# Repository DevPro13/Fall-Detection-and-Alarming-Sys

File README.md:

# Fall Detection and Alerting System

> "Fall seven times, stand up eight." - Japanese Proverb

While the proverb speaks of resilience, falls can be a critical health concern, especially for the elderly. This project presents a robust fall detection system that combines wearable technology and machine learning to provide timely alerts, mitigating the risks associated with delayed assistance.

This system is built upon the research detailed in the paper [**"Fall Detection System for Elderly People Using LSTM"**](https://www.nepjol.info/index.php/joeis/article/view/93497), [Alternate Link](https://www.researchgate.net/publication/404278061_Fall_Detection_System_for_Elderly_People_Using_LSTM). *(Link to full paper — https://www.nepjol.info/index.php/joeis/article/view/93497 or https://www.researchgate.net/publication/404278061_Fall_Detection_System_for_Elderly_People_Using_LSTM)* It leverages a custom-designed wearable device to monitor user movement and a sophisticated deep learning model to accurately distinguish between normal daily activities and dangerous falls.

The system is architecturally divided into two main sub-systems:
-   **Wearable Detector:** A compact, body-worn device that captures real-time motion data.
-   **System Groundstation:** A stationary unit that receives alerts from the wearable and triggers local alarms.

## System Activity Diagram
The operational flow of the system is as follows:

## Wearable Detector

This is the core data acquisition and processing unit of the system. It is designed to be worn on the user's shoulder—a location chosen to minimize motion impedance and ensure stable, accurate readings. The device continuously captures motion data, processes it with an onboard machine learning model, and transmits an alert if a fall is detected.

**Key Components:**
*   **Microcontroller:** Raspberry Pi Pico (RP2040)
*   **Sensor:** MPU-6050, a 6-axis Inertial Measurement Unit (IMU) that provides accelerometer and gyroscope data.
*   **Wireless Communication:** The hardware is designed with a dedicated slot for an HC-05 Bluetooth module to transmit alerts wirelessly to the groundstation.
*   **Power Supply:** The device can be powered via a DC source (regulated by an LM7805 IC) or a direct USB connection.

### Machine Learning Model

The intelligence of the system lies in its fall detection model. Instead of simple thresholds, this project employs a **Long Short-Term Memory (LSTM)** neural network, a type of recurrent neural network (RNN) ideal for analyzing sequential data like human motion.

*   **Model Architecture:** The final system uses a refined **double-layer LSTM model**. This architecture proved significantly more effective than an initial single-layer model, demonstrating a superior ability to learn the complex temporal patterns that differentiate a fall from other activities.
*   **Data Collection:** The model was trained on a dataset created by capturing sequential motion data from participants mimicking the daily activities of the elderly (walking, sitting, standing) as well as simulated fall events.
*   **Performance:** The double-layer LSTM model achieved an impressive **accuracy of 97.8%**. More critically, it demonstrated high sensitivity in identifying falls, reducing the dangerous instances of false negatives that plagued simpler models.

| Metric | 1-Layer LSTM Model | 2-Layer LSTM Model |
| :--- | :--- | :--- |
| **Accuracy** | 92.19% | **97.8%** |
| **Sensitivity (Recall)** | 38.37% | **91.86%** |
| **Precision** | 75.00% | **87.78%** |
| **F1-Score** | 50.77% | **89.77%** |

The trained model is deployed directly onto the Raspberry Pi Pico, allowing for real-time, on-device inference without reliance on a constant internet connection.

### PCB Design

## System Groundstation

The groundstation acts as the central alerting hub. It remains in a fixed location within the user's home, listening for signals from the wearable device. Upon receiving a fall alert, it triggers both audible and visual alarms to notify nearby caregivers.

**Key Components:**
*   **Microcontroller:** Atmega328p
*   **Wireless Communication:** An RF/Bluetooth receiver to communicate with the wearable device.
*   **Alerting Peripherals:** A loud buzzer and bright LEDs.
*   **Power Supply:** 5V DC power, supplied by the custom rectifier circuit below.

## Power Supply Rectifier

This custom circuit was designed to provide a stable, regulated 5V DC supply for the groundstation from an AC source.

**Components:**
*   Bridge Rectifier (Diodes)
*   LM7805 Voltage Regulator
*   Smoothing Capacitors
*   Resistor

### PCB Design

## Authors

- **Sanim Kumar Khatri** - [GitHub](https://github.com/SanimKumarKhatri)
- **Devraj Parajuli** - [GitHub](https://github.com/DevPro13)
- **Bhupendra Chaulagain**- [Github](https://github.com/BhupendraChaulagain)
- **Prayag Man Mane** - [Github](https://github.com/gityag)
- **Sandesh Thapa** - [Github](https://github.com/sandeshit)\
IOE, Pulchowk Campus

## License

This project is released for academic and research purposes. Hardware designs and firmware are provided as-is.

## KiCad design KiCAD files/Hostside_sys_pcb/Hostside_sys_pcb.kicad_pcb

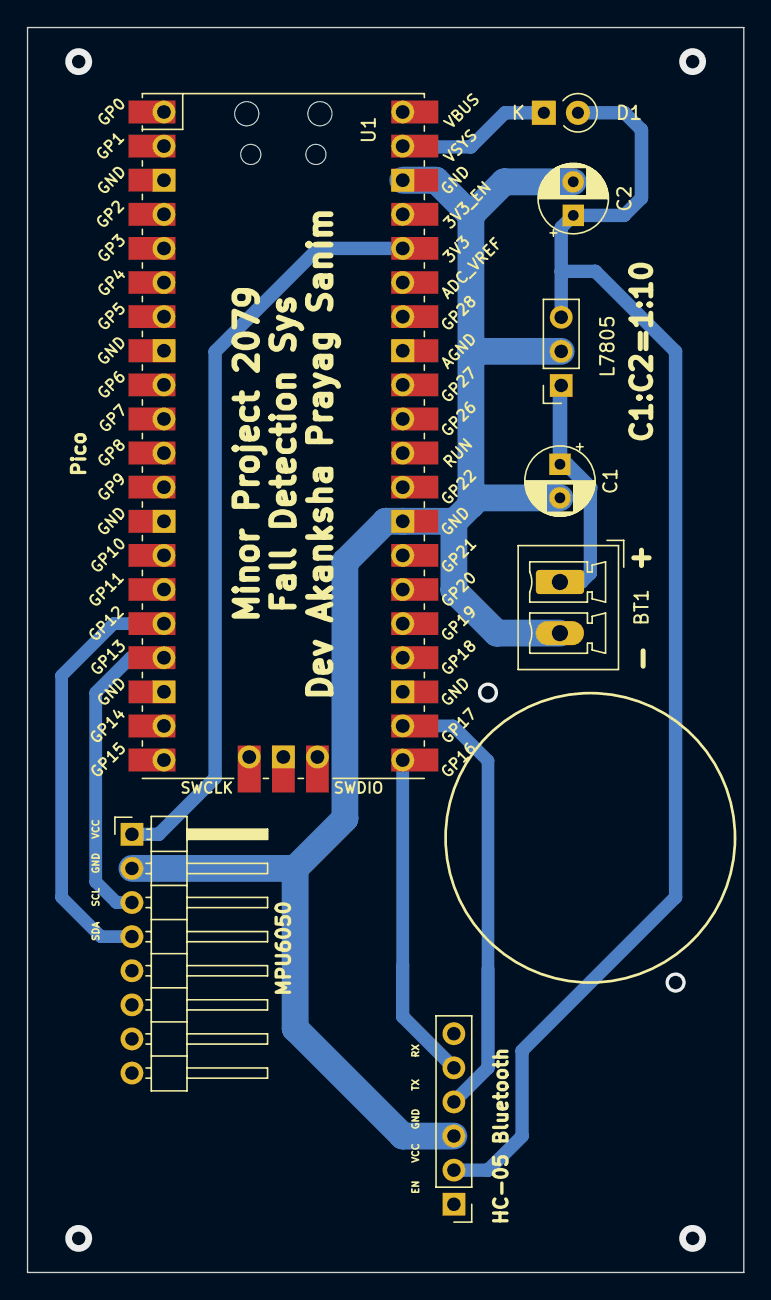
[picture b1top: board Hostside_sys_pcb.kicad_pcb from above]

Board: 2 copper layers, 53.3 x 92.7 mm, 8 parts (0 on the bottom side), 9 nets.

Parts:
BT1: Battery_Cell; PhoenixContact_MCV_1,5_2-G-3.81_1x02_P3.81mm_Vertical
C1, C2: C; CP_Radial_D5.0mm_P2.50mm
D1: MBR1020VL; D_A-405_P2.54mm_Vertical_KathodeUp
HC-05 Bluetooth: Conn_01x06_Female; PinHeader_1x06_P2.54mm_Vertical
MPU6050: Conn_01x08_Female; PinHeader_1x08_P2.54mm_Horizontal
U1: Pico; RPi_Pico_SMD_TH
U2: L7805; PinSocket_1x03_P2.54mm_Vertical

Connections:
/SCL: MPU6050.3, U1.17 (GPIO13)
/SDA: MPU6050.4, U1.16 (GPIO12)
/VCC_3.3: MPU6050.1, U1.36 (3V3)
/Vin_5V: C2.1, D1.2 (A), HC-05 Bluetooth.2, U2.3 (OUT)
/rx: HC-05 Bluetooth.4, U1.22 (GPIO17)
/tx: HC-05 Bluetooth.5, U1.21 (GPIO16)
GND: BT1.2 (-), C1.2, C2.2, HC-05 Bluetooth.3, MPU6050.2, U1.28 (GND), U1.38 (GND), U2.2 (GND)
unnamed: BT1.1 (+), C1.1, U2.1 (IN)
unnamed: D1.1 (K), U1.39 (VSYS)

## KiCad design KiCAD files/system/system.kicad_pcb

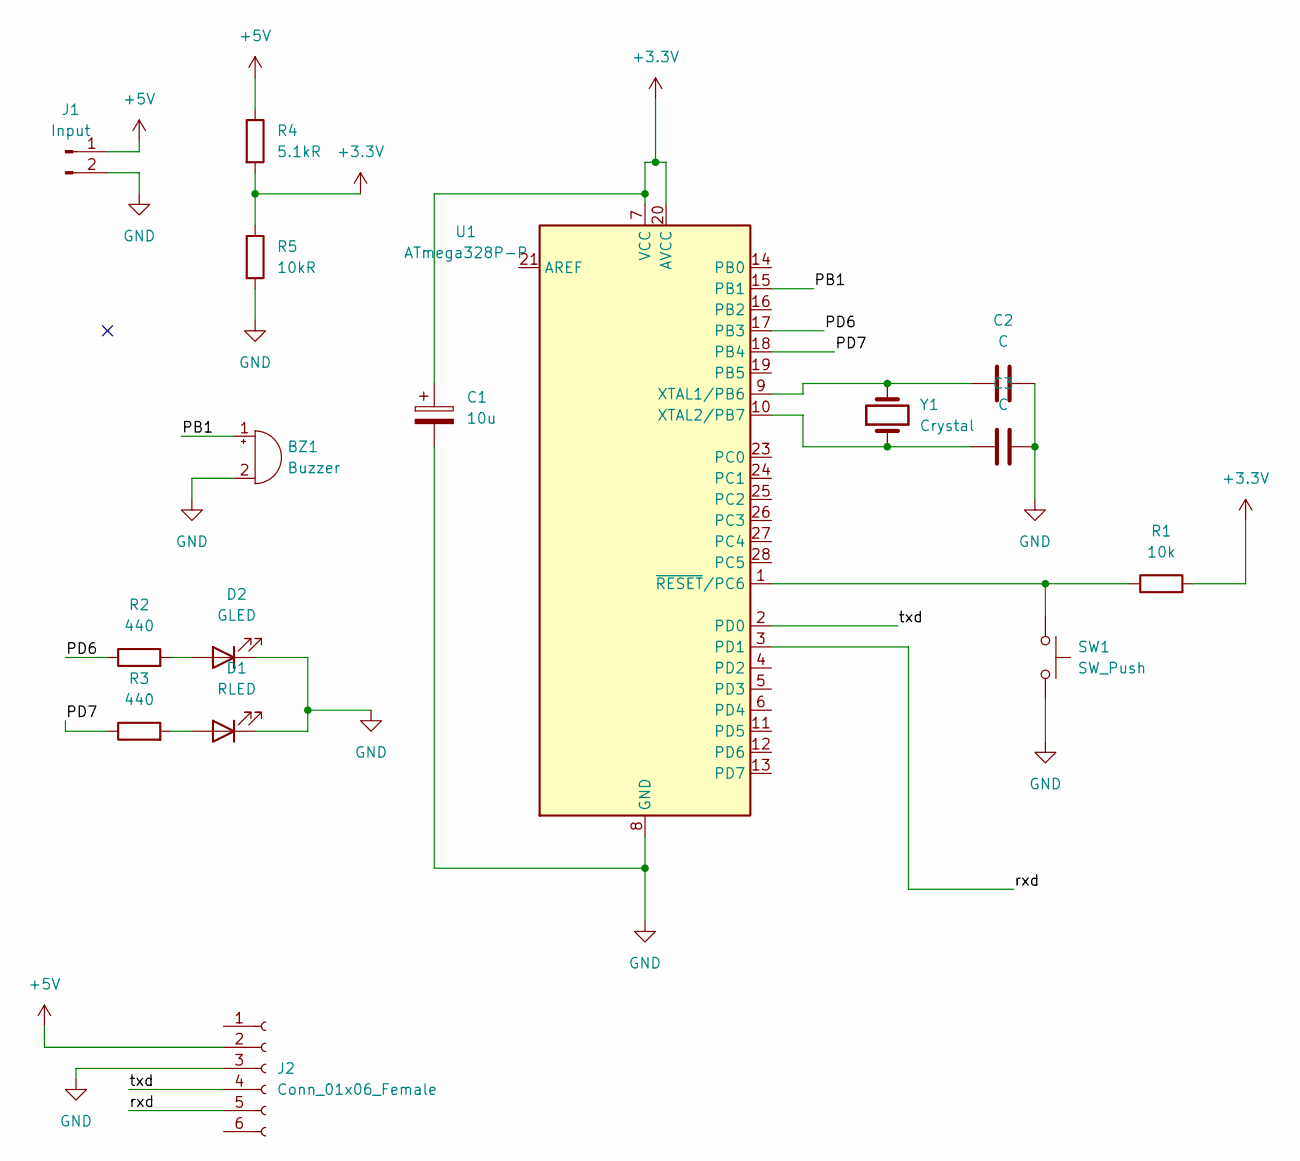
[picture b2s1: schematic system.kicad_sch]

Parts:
BZ1: Buzzer; MagneticBuzzer_ProSignal_ABT-410-RC
C1: 10u; CP_Radial_D5.0mm_P2.00mm
C2, C3: C; C_Disc_D7.0mm_W2.5mm_P5.00mm
D1: RLED; LED_D5.0mm
D2: GLED; LED_D5.0mm
J1: Input; R_Axial_DIN0411_L9.9mm_D3.6mm_P5.08mm_Vertical
J2: Conn_01x06_Female; PinHeader_1x06_P2.54mm_Vertical
R1: 10k; R_Axial_DIN0207_L6.3mm_D2.5mm_P10.16mm_Horizontal
R2, R3: 440; R_Axial_DIN0207_L6.3mm_D2.5mm_P10.16mm_Horizontal
R4: 5.1kR; R_Axial_DIN0207_L6.3mm_D2.5mm_P10.16mm_Horizontal
R5: 10kR; R_Axial_DIN0207_L6.3mm_D2.5mm_P10.16mm_Horizontal
SW1: SW_Push; SW_PUSH_6mm
U1: ATmega328P-P; DIP-28_W7.62mm
Y1: Crystal; R_Box_L8.4mm_W2.5mm_P5.08mm

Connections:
+3.3V: C1.1, R1.2, R4.2, R5.1, U1.7 (VCC), U1.20 (AVCC)
+5V: J1.1, J2.2, R4.1
/PB1: BZ1.1 (-), U1.15 (PB1)
/PD6: R2.1, U1.17 (PB3)
/PD7: R3.1, U1.18 (PB4)
/rxd: J2.5, U1.3 (PD1)
/txd: J2.4, U1.2 (PD0)
GND: BZ1.2 (+), C1.2, C2.2, C3.2, D1.1 (K), D2.1 (K), J1.2, J2.3, R5.2, SW1.2, U1.8 (GND), U1.22 (GND)
unnamed: C2.1, U1.9 (XTAL1/PB6), Y1.2
unnamed: C3.1, U1.10 (XTAL2/PB7), Y1.1
unnamed: D1.2 (A), R3.2
unnamed: D2.2 (A), R2.2
unnamed: R1.1, SW1.1, U1.1 (~RESET/PC6)

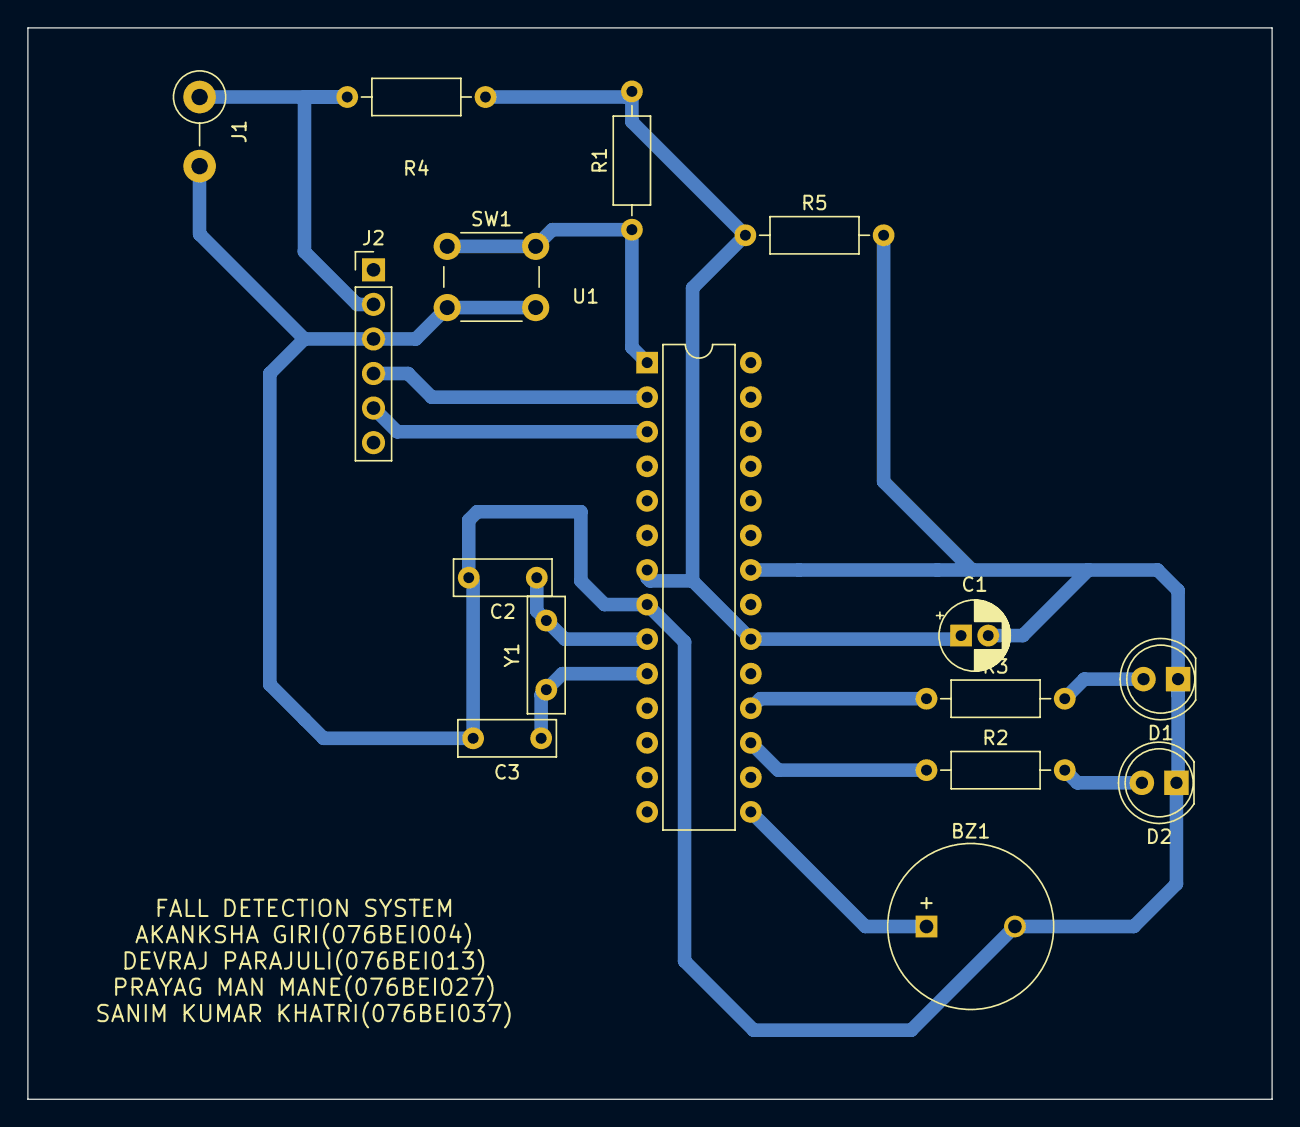
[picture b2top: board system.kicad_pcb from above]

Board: 2 copper layers, 91.4 x 78.7 mm, 16 parts (0 on the bottom side), 13 nets.

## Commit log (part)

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2023-01-15 Added gitignore file and simulation
    simulation of bridge rectifier and regulator
2023-01-15 Bridge rectifier (KiCAD) added
2023-01-15 Added resources
    For bridge rectifier and regulator
2023-01-30 Host side PCB design files added
2023-02-03 started system side pcb
    this is initial phase, more updates are needed on this pcb
2023-02-08 Edited Rectifier schematics and PCB
    edited the trackwidth from 1mm to 1.5mm
2023-02-08 Edited system schematics
2023-02-08 Edited PCB
2023-02-08 Hostside pcb front and back images and PCB_prints pdf files added into resources
2023-02-08 host side kicad files added and updated
2023-02-08 hostside_front pcb_print made mirrored and added
2023-02-08 tracks between distance updated for scl and sda lines and capacitor pin size updated and pcb_ prints pdf files added
2023-02-08 Hostside kicad files updated and added
2023-02-09 Rectiier ckt bug fixed
2023-02-09 Edited rectifier pcb
2023-02-09 clearance updated in hostside pcb
2023-02-16 Edited system pcb layout
2023-02-16 Update schematics of system
2023-03-04 use case diagram added
2023-03-04 Use case and Sequence diagram added
2023-03-04 Added png of umls
2023-03-04 Edited activity diagram
2023-03-04 Edited use case diagram
2023-03-04 edited sequence diagram
2023-03-04 sequence diagram updated
2023-03-04 added class diagram
2023-03-04 Case study documents on Fall detection system added
2023-03-08 edited oops
2023-03-08 Create fall
2023-03-08 Create run
2023-03-08 Create walk
2023-03-08 Create code
2023-03-09 edited the system side circuit
2023-03-09 rename run to run1
2023-03-11 new dataset files added
2023-03-12 new dataset added
2023-03-18 edited system side pcb
2023-03-22 edited system pcb
2023-03-22 final draft of the system side pcb
2023-03-22 halka edit smoothing capacitor ma
2023-03-23 edited the print images
2023-03-23 print images added for system
2023-03-23 Host side pcb updates
2023-03-23 edited size of capacitor footprint
2023-03-23 files merge
2023-03-24 updated the pdf of pcb
2023-03-24 rectifier pcb prints update
2024-12-06 Dataset for LSTM added.
2024-12-06 Data logging code added
2024-12-11 Bug fixed: Issue regarding data logging and elapsed time.
2024-12-11 Removed Dataset
2024-12-11 Code updated: modified in elapsed time setup
2026-05-10 Hardware Image Upload
